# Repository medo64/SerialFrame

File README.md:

[Isolated UART Framework Expansion Card](https://medo64.com/uartisowork/)
=========================================================================

This Framework laptop expansion card will show up on your system as a serial
device and allow for a fully isolated serial UART communication up to 1 Mbaud
rate.

Please note that this card is not using RS-232 but TTL (either 3.3V or 5V)
voltage levels (depending on the solder-jumper position).

## UART Pinout

To connect to this board, one has to use 3-pin JST XH connector. The following
table represents the pinout, pin 1 being on the left as looking into the
expansion card.

| # | Ref | Description                     |
|--:|:---:|---------------------------------|
| 1 | RXD | Receive (TTL: 5V or 3.3V)       |
| 2 | GND | Ground connection               |
| 3 | TXD | Transmit (TTL: 5V or 3.3V)      |

PPS: As power consumption is below 10 mA, wires can be almost any AWG. I would
recommend using 24 AWG wire (0.25 mm²) as they allow for greater compatibility
with other connectors.

## Supported Speeds

This board employs the FT232R as its UART chip, and consequently, it supports
all the baud rates this chip [can handle](https://ftdichip.com/Documents/AppNotes/AN232B-05_BaudRates.pdf)
up to 1 Mbaud which is the limit of isolator chip used. The table below lists
the standard baud rates.

| Baud rate |    Actual | Error |    Divisor |
|----------:|----------:|------:|-----------:|
|       300 |       300 | 0.00% |  10000.000 |
|       600 |       600 | 0.00% |   5000.000 |
|     1,200 |     1,200 | 0.00% |   2500.000 |
|     1,800 |     1,800 | 0.00% |   1666.625 |
|     2,400 |     2,400 | 0.00% |   1250.000 |
|     4,800 |     4,800 | 0.00% |    625.000 |
|     7,200 |     7,201 | 0.01% |    416.625 |
|     9,600 |     9,600 | 0.00% |    312.500 |
|    14,400 |    14,406 | 0.04% |    208.250 |
|    19,200 |    19,200 | 0.00% |    156.250 |
|    28,800 |    28,812 | 0.04% |    104.125 |
|    38,400 |    38,400 | 0.00% |     78.125 |
|    57,600 |    57,692 | 0.16% |     52.000 |
|   115,200 |   115,385 | 0.16% |     26.000 |
|   230,400 |   230,769 | 0.16% |     13.000 |
|   460,800 |   461,538 | 0.16% |      6.500 |
|   921,600 |   923,077 | 0.16% |      3.250 |

---
*You can check my blog and other projects at [www.medo64.com](https://www.medo64.com/electronics/).*

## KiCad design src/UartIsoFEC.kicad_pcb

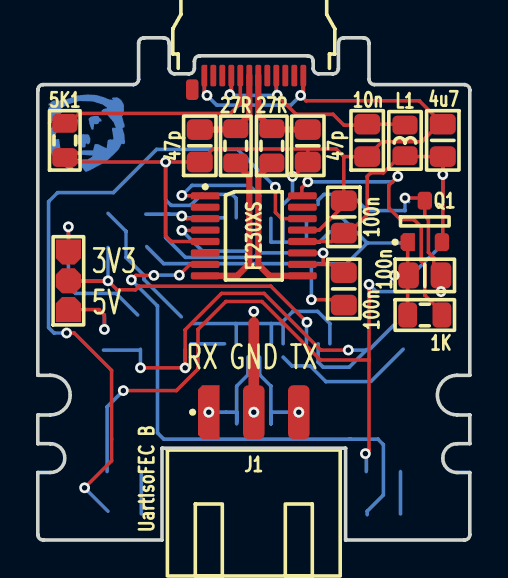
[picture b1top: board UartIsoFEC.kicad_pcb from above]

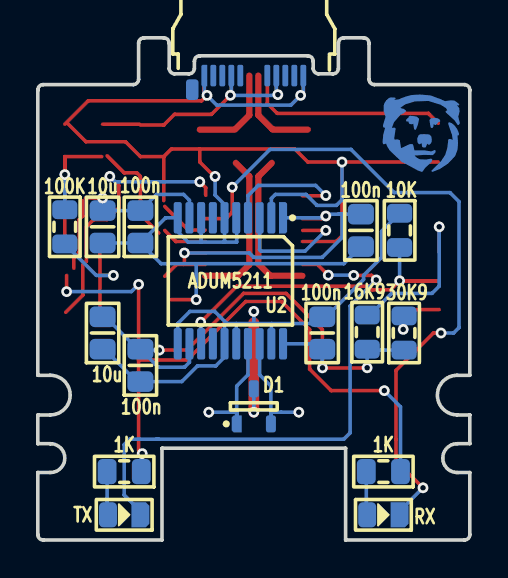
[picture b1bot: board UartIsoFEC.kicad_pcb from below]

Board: 2 copper layers, 24.0 x 27.9 mm, 34 parts (17 on the bottom side), 25 nets.

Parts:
C1, C2: 47p; C (0805)
C3: 10n; C (0805)
C4, C5, C6, C7, C8, C9, C10: 100n; C (0805)
C11: 4u7; C (0805)
C12, C13: 10u; C (0805)
D1: SM05T1G; D TVS SM05T1G (SOT23-3)
DS1: RX; DS (0805)
DS2: TX; DS (0805)
ICON: Medo64; ICON Medo64
J1: B3B-XH-A; J JST XH Edge [UART] (3w)
JP1: Jumper; JP Dual (1205)
L1: 600R; L (0805)
P1: 105444-0001; P USB C 3.2 Edge (24w)
Q1: DMP3099L-13; Q MOSFET-P (SOT23-3)
R1, R2: 27R; R (0805)
R3, R4, R5: 1K; R (0805)
R6: 5K1; R (0805)
R7: 10K; R (0805)
R8: 16K9; R (0805)
R9: 30K9; R (0805)
R10: 100K; R (0805)
U1: FT230XS; U Transciever UART FT230XS (SSOP-16)
U2: ADUM5211; U Isolator+Power ADUM5211ARSZ (SSOP-20)

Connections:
3V3: C5.2, C8.2, U1.3, U1.10, U1.11, U2.1
5V: C4.2, C11.2, L1.1, Q1.2, R10.1, U1.12
5V_SWITCHED: C6.2, C7.2, C12.2, Q1.3, R3.1, R4.1, U2.9
GND: C1.1, C2.1, C3.1, C4.1, C5.1, C7.1, C8.1, C11.1, C12.1, P1.A1, P1.A12, P1.B01, P1.B12, R6.1, U1.5, U1.13, U2.2, U2.5, U2.6, U2.8, U2.10
ISO_GND: C9.1, C10.1, C13.1, D1.3, J1.2, R7.1, U2.11, U2.15, U2.16, U2.19
ISO_RX: D1.2, J1.1, U2.18
ISO_TX: D1.1, J1.3, U2.17
ISO_V+: C9.2, C10.2, C13.2, R8.1, R9.1, U2.12, U2.20
ISO_V_SELECT: JP1.2, R7.2, U2.13
ISO_V_SELECT_3V3: JP1.3, R8.2
ISO_V_SELECT_5V: JP1.1, R9.2
LED_RX: DS1.1, U1.14
LED_RX': DS1.2, R3.2
LED_TX: DS2.1, U1.7
LED_TX': DS2.2, R4.2
PWREN#: R5.2, U1.16
PWREN#': C6.1, Q1.1, R5.1, R10.2
RX: U1.4, U2.3
TX: U1.1, U2.4
USB_CC: P1.A5, R6.2
USB_DM: C2.2, P1.A7, R2.2
USB_DM': R2.1, U1.9
USB_DP: C1.2, P1.A6, R1.2
USB_DP': R1.1, U1.8
USB_V+: C3.2, L1.2, P1.A4, P1.A9, P1.B04, P1.B09

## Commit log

2022-04-02 Added reverse voltage protection diode
2022-04-02 LED on by default
2022-04-02 Using MOSFET for reverse protection
2022-04-02 Updated MOSFET
2022-04-02 Added wiring text file
2022-04-04 Changed font to Bahnschrift
2022-04-18 Moving LEDs a bit
2022-04-18 Renamed project
2022-05-07 Removed extra CC2 resistor
2022-05-09 Changed connector to XH variant
2022-05-09 Added case STLs
2022-05-15 Changing isolator to Adum1281
2022-05-15 Updated case STLs
2023-09-17 Initial layout
2023-09-18 New revision using FT260X
2023-09-18 Added protection diode
2023-10-10 Larger silkscreen markings
2023-10-25 Updated footprints
2023-10-30 Added config files
2023-10-30 Rotated CC resistor
2023-10-30 Increased drive current
2023-11-03 Updated net names
2023-11-04 Added RTS/CTS loopback
2023-11-13 Moved LEDs to bottom
2023-12-26 Refactored LED control
2023-12-26 Removed internal RTS/CTS connection
2023-12-26 Added missing PWREN pullup resistor
2023-12-30 Minor cleanup and expanding soldermask
2024-01-31 Moved LEDs
2024-01-31 Moved board RefDes to top
